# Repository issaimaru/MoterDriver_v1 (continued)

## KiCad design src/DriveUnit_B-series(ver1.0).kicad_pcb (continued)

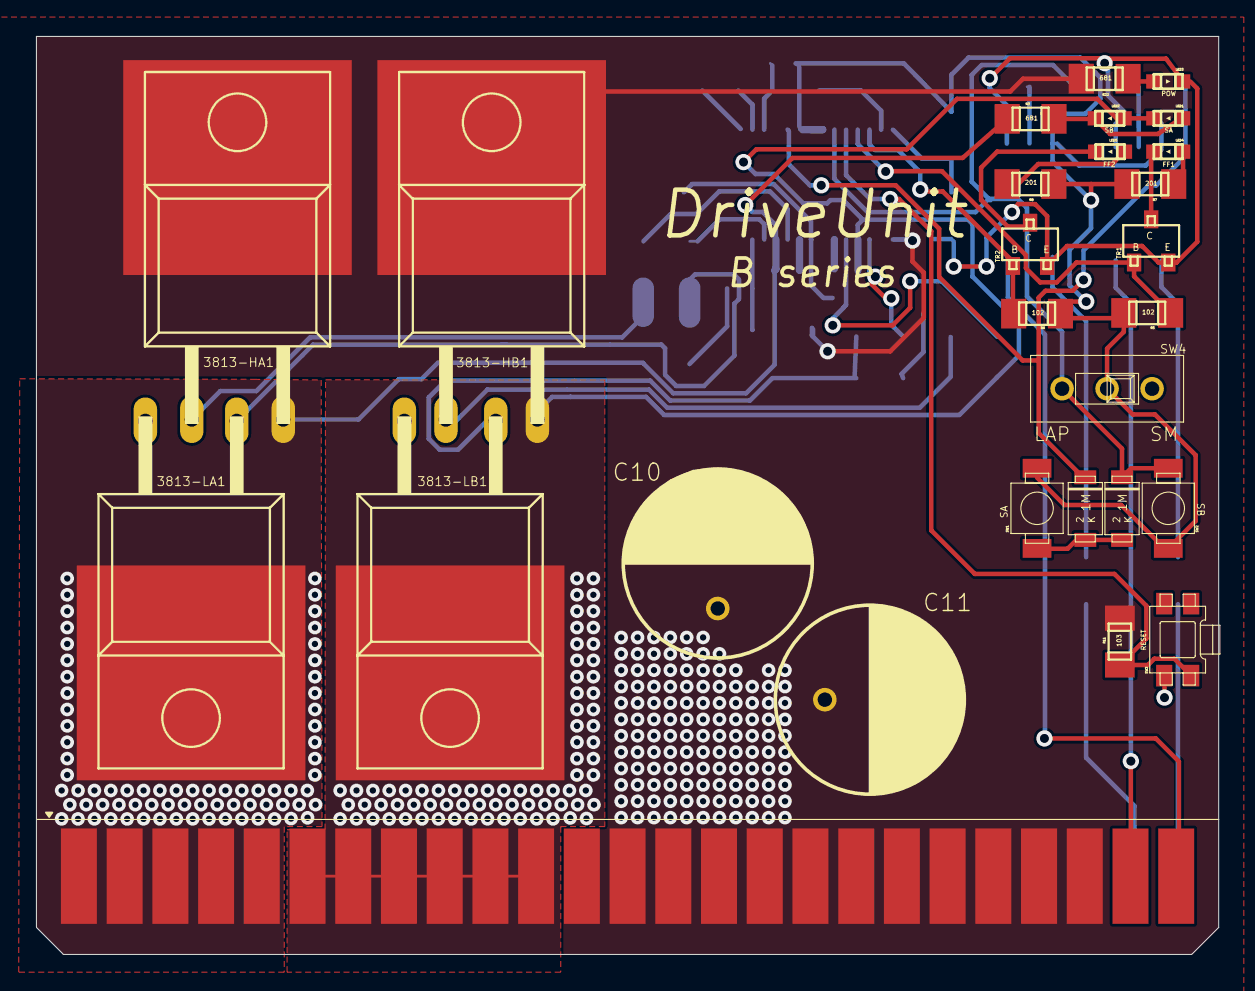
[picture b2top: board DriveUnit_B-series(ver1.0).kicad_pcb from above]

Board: 2 copper layers, 65.7 x 51.0 mm, 57 parts (0 on the bottom side), 41 nets.

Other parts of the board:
R4, R17: RG2012N-201-W-T1; RG2012

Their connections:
/DIR_IN: R4.RIGHT; also elsewhere on the board
/VCC_IN: R17.RIGHT; also elsewhere on the board
unnamed 40: R4.LEFT; also elsewhere on the board
unnamed 42: R17.LEFT; also elsewhere on the board

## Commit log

2022-05-14 Create LICENSE
2022-05-15 brd編集 配線
2022-05-17 部品配置訂正 大電流パターン考慮
2022-05-17 edit:配線の追加
2022-05-18 edit:GND,VCCベタ,wireの追加
2022-05-19 edit:大体配線完了
2022-05-23 ビアの配置
2022-05-25 ビア,パターンの追加 ほぼ完成
2022-05-29 GNDパターンの強化
2022-06-15 配線の追加,整理
2022-06-16 配線を太くした
2022-06-17 配線完了
2022-06-17 KiCadへの移行,PCBデザインの完成
2022-06-18 配線の修正等
2022-06-18 DRCエラーの対処
2022-06-23 基板デザインの完成
2022-06-24 Update README.md
    部品のリストを更新
2022-06-24 Update README.md
    使用電子部品，及びその値段の表の追加
2022-06-24 Update README.md
    総額の追加
2022-06-24 Update README.md
    前モタドラとの違いを記述
2022-06-25 Update README.md
    回路図の追加
2022-06-25 gerberの出力,名前の変更
2022-06-25 fp-info-cacheの更新
2022-06-26 名前の変更
2022-06-28 Update README.md
    回路図のクローン方法の追加
2022-06-30 Eagle_ERCエラーの修復
2022-06-30 Update README.md
    説明の追加
2022-06-30 Update README.md
    linkの更新
2022-07-01 意図的なconflict
2022-07-01 conflict前段階
2022-07-01 意図conflict new側
2022-07-01 conflict old側
2022-07-01 背面パッドの考慮
2022-07-01 conflict解消 サーマルパッドの考慮
2022-07-01 gerberの更新
2022-07-01 Update .gitignore
    Eagleの追加
2022-07-02 GNDベタの修正
2022-07-02 ガバ設計による炎上回避(GNDベタを大きくした)
2022-07-02 シルクの修正
2022-07-02 Update README.md
    FFXピンの説明
2022-07-03 FF2の配線の修正
2022-07-05 フォトカプラLED入力に200ohm抵抗付けた
2022-07-05 Update README.md
    表の画像の修正
2022-07-06 Update README.md
    R4，R17の追加
2022-07-09 Update README.md
    ページの追加，敬語
2022-07-11 Update README.md
    機能の説明の追加
2022-08-04 説明の追加
2022-08-05 readme.mdの編集
2022-08-05 折りたたみの追加
2022-08-06 readme.mdに不具合の追加
2022-08-06 Update README.md
    ミスの修正
2022-08-06 Update LICENSE
2022-08-08 Update README.md
    修正点の追加
2022-08-11 はんだ付けの仕方の説明の追加
2022-08-12 read.me更新
2022-08-12 readme.mdの更新
2022-08-14 ヒートガンリフローの説明の追加
2022-08-14 はんだ付けの説明終了
2022-08-30 [fix]入力周りなどの変更(ver1.0の問題点の修復)
2022-09-01 入力部分の追加
2022-09-01 README_v1等の追加
2022-09-01 回路図の偏向
2022-09-02 [fix]デッドタイムを100kΩ可変抵抗で調整できるように変更
2022-09-02 [add]電流センサ周りの配線_1
2022-09-15 [remove:電流センサを取り除いた
2022-09-15 [add]配線の追加
2022-09-16 入力部の配線の追加
2022-09-16 [add]部品配置完了
2022-09-16 [add]9/16進捗分
2022-09-18 配線の追加
2022-09-19 ビアなどの追加
2022-09-19 SA，SBベタ以外は配線終了．
2022-09-20 配線の終了
2022-09-20 モタドラ配線完全終了_KiCad移行前
2022-09-20 kicad完全移行_シルク配置全完
2022-09-20 デザイン完了
2022-09-21 ver2.0完全完了_gerber出力前
2022-09-21 ver2.0ちょい修正_gerber出力前
2022-09-21 gerber出力完了
2022-09-22 回路ミスってた(嘘だろ...)_KiCad以降前
2022-09-22 修正前ファイルを消した_KiCad以降前
2022-09-22 KiCad移行後_schファイル破壊
2022-09-22 KiCad移行後_破壊ファイルの修正
2022-09-22 表デザイン完成
2022-09-22 デザイン途中まで
2022-09-23 基板デザインの完全完成_gerber出力前
2022-09-23 gerber出力後
2022-09-23 gerber出力 一応もう一回(え？)
2022-09-24 readmeの更新
2022-09-27 markdownの更新
2022-09-28 markdown_v2の更新3
